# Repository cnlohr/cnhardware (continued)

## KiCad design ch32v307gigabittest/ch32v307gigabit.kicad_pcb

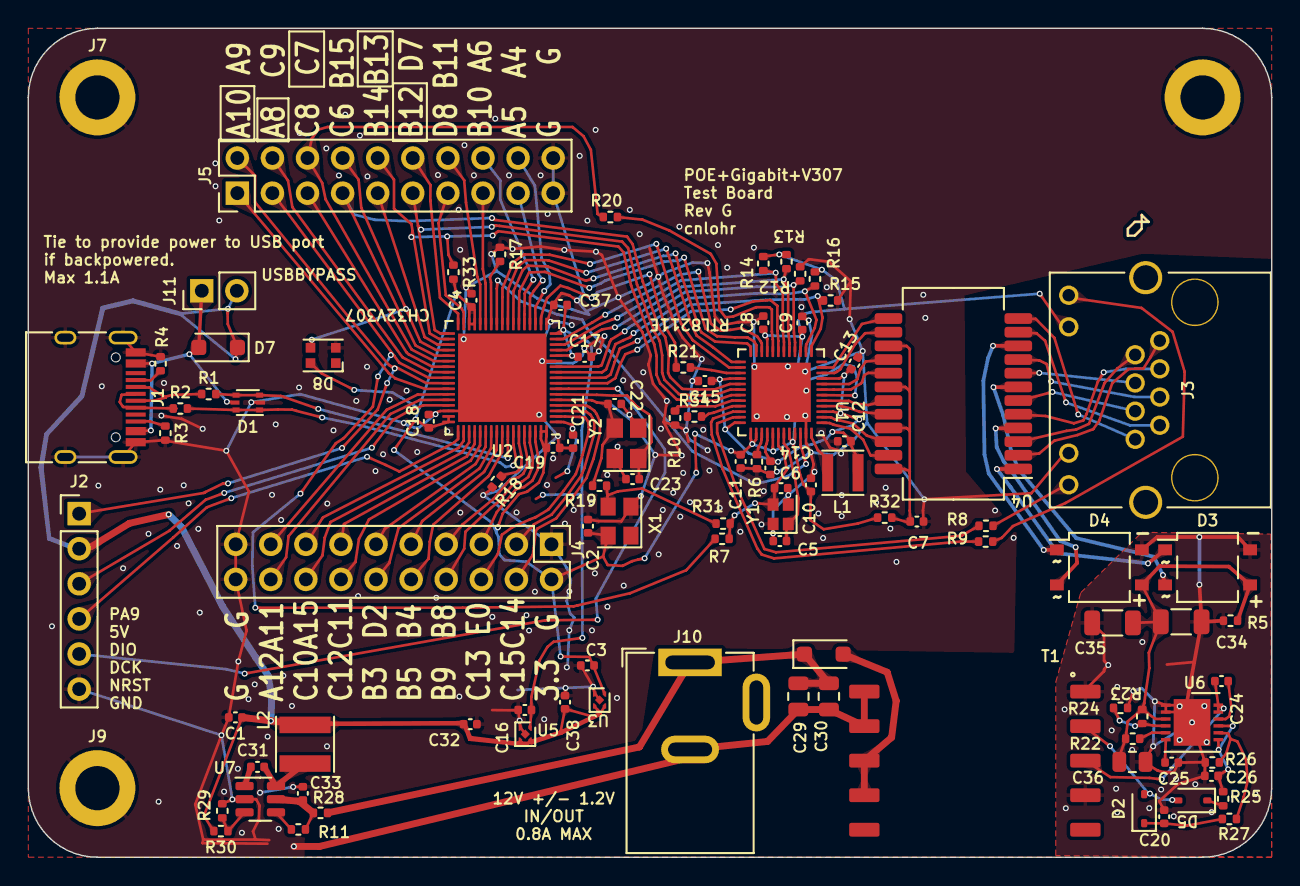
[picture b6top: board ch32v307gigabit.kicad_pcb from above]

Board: 2 copper layers, 90.0 x 60.0 mm, 101 parts (0 on the bottom side), 120 nets.

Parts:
C1, C3, C8, C12, C16, C21, C32: 4.7u; C_0402_1005Metric
C2, C26: 1u; C_0402_1005Metric
C4, C9, C10, C11, C13, C14, C15, C17, C18, C19, C25, C33, C37, C38: 0.1u; C_0402_1005Metric
C5, C6, C22, C23: 10p; C_0402_1005Metric
C7, C20, C24: 10n; C_0402_1005Metric
C29, C30: 25v10u; C_0805_2012Metric
C31: 22n; C_0402_1005Metric
C34, C35: 2.2u100v; C_1206_3216Metric
C36: 100v100n; C_0805_2012Metric
D1: USBLC6-2P6-TVS; SOT-666
D2, D5: D_SOD-323
D3, D4: RMBF; TO-269AA
D6, D7: D_SOD-123F
D8: WS2812B-2020; LED_WS2812B-2020_PLCC4_2.0x2.0mm
J1: USB_C_Receptacle_USB2.0; USB_C_Receptacle_HRO_TYPE-C-31-M-12
J2: PGM; PinHeader_1x06_P2.54mm_Vertical
J3: R-RJ45R08P-C000
J4, J5: AUX; PinHeader_2x10_P2.54mm_Vertical
J7, J8, J9: MH; MountingHole_3.2mm_M3_ISO14580_Pad
J10: Barrel; BarrelJack_GCT_DCJ200-10-A_Horizontal
J11: USBBYPASS; PinHeader_1x02_P2.54mm_Vertical
L1: 2.2uH 1.6A; L_Taiyo-Yuden_MD-3030
L2: 6.8uH 2A; L_Taiyo-Yuden_MD-4040
R1, R2, R25: 22; R_0402_1005Metric
R3, R4, R11: 5.1k; R_0402_1005Metric
R5, R24: 25k; R_0402_1005Metric
R6, R26, R29: 2.49k 1%; R_0402_1005Metric
R7, R19, R20, R21, R28: 0; R_0402_1005Metric
R8, R9: 1k; R_0402_1005Metric
R10, R12, R13, R14, R15, R16, R17, R18, R33: 4.7k; R_0402_1005Metric
R22, R23: 390k; R_0402_1005Metric
R27: 10k; R_0402_1005Metric
R30: 18k 1%; R_0402_1005Metric
R31, R32, R34: NP; R_0402_1005Metric
T1: TNK-TSA021-POE-TRANSFORMER
U1: RTL8211E-VB-CG; QFN-48-1EP_6x6mm_P0.4mm_EP4.3x4.3mm
U2: QFN-68-0.2mmpads-1EP_8x8mm_P0.4mm_EP6.4x6.4mm
U3, U5: 3.3vReg; xdfn-reg
U4: Transformer_Ethernet_YDS_30F-51NL_SO-24_7.1x15.1mm
U6: LM5160ADNTR; DFN-12-1EP_4x4mm_P0.5mm_EP2.66x3.38mm
U7: MT2492; SOT-23-6
X1: 8MHz TCXO; Oscillator_SMD_Abracon_ASE-4Pin_3.2x2.5mm
Y1: 25MHz; Crystal_SMD_2016-4Pin_2.0x1.6mm
Y2: 8MHz12pF; Crystal_SMD_3225-4Pin_3.2x2.5mm

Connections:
+3.3VA: C16.1, C17.1, C37.1, U2.13 (VDDA), U2.17 (VIO_4), U5.1 (OUT)
+3V3: C2.1, C3.1, C4.1, C8.1, C9.1, C10.1, C11.1, C18.1, C19.1, D8.4 (VDD), J3.10, J4.2, R13.2, R14.2, R16.2, R32.1, R33.2, U1.6 (AVDD33), U1.15 (DVDD33), U1.21 (DVDD33), U1.37 (DVDD33), U1.38 (ENSWREG), U1.41 (AVDD33), U1.44 (VDDREG), U1.45 (VDDREG), U2.31 (VIO_1), U2.32 (VDD_1), U2.50 (VDD_2), U2.51 (VIO_2), U2.67 (VIO_3), U2.68 (VDD_3), U3.1 (OUT), X1.4 (Vdd)
+5V: C1.1, C32.1, C38.1, D7.1 (K), J2.2, J11.2, L2.2, R30.2, U3.3 (EN), U3.4 (IN), U5.3 (EN), U5.4 (IN)
+12V: C29.1, C30.1, D6.1 (K), J10.1, R28.2
CT1: D4.1, U4.10 (MCT4)
CT2: D3.1, U4.1 (MCT1)
CT3: D4.2, U4.4 (MCT2)
CT4: D3.2, U4.7 (MCT3)
D+: D1.1 (IO1), D1.6 (IO1), R2.2, U2.62 (PB7/USB2DP)
D-: D1.3 (IO2), D1.4 (IO2), R1.2, U2.61 (PB6/USB2DM)
EPA4: J5.18, U2.20 (PA4/ADC4/DAC0)
EPA5: J5.17, U2.21 (PA5/ADC5/DAC1)
EPA6: J5.16, U2.22 (PA6/ADC6)
EPA9: J2.1, J5.2, U2.44 (PA9)
EPA10: J5.1, U2.45 (PA10)
EPA11: J4.17, U2.46 (PA11/USB1DM)
EPA12: J4.18, U2.47 (PA12/USB1DP)
EPA15: J4.15, U2.53 (PA15)
EPB3: J4.12, U2.58 (PB3)
EPB4: J4.9, U2.59 (PB4)
EPB5: J4.10, U2.60 (PB5)
EPB8: J4.7, U2.64 (PB8)
EPB9: J4.8, U2.65 (PB9)
EPB10: J5.15, U2.29 (PB10)
EPB11: J5.14, U2.30 (PB11)
EPB14: J5.9, U2.37 (PB14)
EPB15: D8.3 (DIN), J5.8, U2.38 (PB15)
EPC7: J5.6, R20.2, U2.40 (PC7/RXN)
EPC8: J5.5, U2.41 (PC8/TXP)
EPC9: J5.4, U2.42 (PC9/TXN)
EPC10: J4.16, U2.54 (PC10)
EPC11: J4.13, U2.55 (PC11)
EPC12: J4.14, U2.56 (PC12)
EPC13: J4.6, U2.2 (PC13)
EPC14: J4.3, U2.3 (PC14)
EPC15: J4.4, U2.4 (PC15)
EPD2: J4.11, U2.57 (PD2)
EPD8: J5.13, U2.33 (PD8)
EPD9: J5.12, U2.34 (PD9)
EPE0: J4.5, U2.66 (PE0)
GMII_CLK125: U1.46 (CLK125), U2.27 (PB1/ADC9)
GMII_MDC: J5.11, U1.30 (MDC), U2.35 (PB12)
GMII_MDIO: J5.10, R33.1, U1.31 (MDIO), U2.36 (PB13)
GMII_RXC: U1.19 (RXC), U2.8 (PC0/ADC10)
GMII_RXCTL: R15.1, U1.13 (RXCTL/PHY_AD), U2.9 (PC1/ADC11)
GMII_RXD0: R16.1, U1.14 (RXD0/SELRGV), U2.10 (PC2/ADC12)
GMII_RXD1: R12.1, U1.16 (RXD1/TXDLY), U2.11 (PC3/ADC13)
GMII_RXD2: R13.1, U1.17 (RXD2/AN0), U2.14 (PA0/ADC0)
GMII_RXD3: R14.1, U1.18 (RXD3/AN1), U2.15 (PA1/ADC1)
GMII_TXC: U1.22 (TXC), U2.16 (PA2/ADC2)
GMII_TXCTL: R21.1, U2.19 (PA3/ADC3)
GMII_TXD0: U1.23 (TXD0), U2.23 (PA7/ADC7)
GMII_TXD1: U1.24 (TXD1), U2.24 (PC4/ADC14)
GMII_TXD2: U1.25 (TXD2), U2.25 (PC5/ADC15)
GMII_TXD3: U1.26 (TXD3), U2.26 (PB0/ADC8)
GND: C1.2, C2.2, C3.2, C4.2, C5.1, C6.1, C7.2, C8.2, C9.2, C10.2, C11.2, C12.2, C13.2, C14.2, C15.2, C16.2, C17.2, C18.2, C19.2, C21.2, C22.1, C23.1, C29.2, C30.2, C32.2, C33.2, C37.2, C38.2, D1.2 (GND), D8.2 (VSS), J1.A1 (GND), J1.A12 (GND), J1.B1 (GND), J1.B12 (GND), J1.S1 (SHIELD), J2.6, J3.11, J4.1, J4.19, J4.20, J5.19, J5.20, J7.1, J8.1, J9.1, J10.2, R3.2, R4.2, R6.2, R10.2, R12.2, R15.2, R17.1, R18.2, R29.1, R34.1, T1.9 (SECA-), T1.10 (SECB-), U1.47 (GND), U1.49 (GND), U2.12 (VSSA), U2.18 (VSS_1), U2.49 (VSS_2), U2.69 (GND), U3.2 (GND), U3.5 (GND), U5.2 (GND), U5.5 (GND), U7.2 (GND), X1.2 (GND), Y1.2, Y1.4, Y2.2, Y2.4
LED0: J3.9, R9.1
LED1: J3.12, R8.1
NRST: J2.5, U2.7 (NRST)
unnamed: D2.2 (A), D5.2 (A), T1.2 (BIAS+)
unnamed: C20.2, D2.1 (K), R27.2
unnamed: D5.1 (K), R25.2
unnamed: J1.A5 (CC1), R4.1
unnamed: J1.B5 (CC2), R3.1
unnamed: J1.A6 (D+), J1.B6 (D+), R2.1
unnamed: J1.A7 (D-), J1.B7 (D-), R1.1
unnamed: C24.2, T1.3 (PRI+), U6.11 (SW), U6.12 (SW)
unnamed: C6.2, R7.2, R31.2, U1.42 (CKXTAL1), Y1.3
unnamed: C5.2, U1.43 (CKXTAL2), Y1.1
unnamed: R20.1, U1.20 (INTB)
unnamed: R9.2, U1.34 (LED0/PHY_AD0)
unnamed: R8.2, U1.35 (LED1/PHY_AD1)
unnamed: U1.1 (MDI[0]+), U4.23 (TX1+)
unnamed: U1.2 (MDI[0]-), U4.22 (TX1-)
unnamed: U1.4 (MDI[1]+), U4.20 (TX2+)
unnamed: U1.5 (MDI[1]-), U4.19 (TX2-)
unnamed: U1.7 (MDI[2]+), U4.17 (TX3+)
unnamed: U1.8 (MDI[2]-), U4.16 (TX3-)
unnamed: U1.10 (MDI[3]+), U4.14 (TX4+)
unnamed: U1.11 (MDI[3]-), U4.13 (TX4-)
unnamed: R34.2, U1.33 (PEMB)
unnamed: L1.1, U1.48 (REG_OUT)
unnamed: R6.1, U1.39 (RSET)
unnamed: R21.2, U1.27 (TXCTL)
unnamed: R18.1, U2.63 (BOOT0)
unnamed: R17.2, U2.28 (PB2/BOOT1)
unnamed: C21.1, U2.1 (VBAT)
unnamed: J3.1, U4.2 (MD1+)
unnamed: J3.2, U4.3 (MD1-)
unnamed: J3.3, U4.5 (MD2+)
unnamed: J3.6, U4.6 (MD2-)
unnamed: J3.4, U4.8 (MD3+)
unnamed: J3.5, U4.9 (MD3-)
unnamed: J3.7, U4.11 (MD4+)
unnamed: J3.8, U4.12 (MD4-)
unnamed: C7.1, R32.2, U4.15 (TCT4), U4.18 (TCT3), U4.21 (TCT2), U4.24 (TCT1)
unnamed: C24.1, U6.10 (BST)
unnamed: R23.2, R24.1, U6.4 (EN/UVLO)
unnamed: R26.2, R27.1, U6.8 (FB)
unnamed: C26.1, R25.1, U6.7 (FPWM), U6.9 (VCC)
unnamed: R22.2, U6.5 (RON)
unnamed: C25.1, U6.6 (SS)
unnamed: C31.1, U7.1 (BS)
unnamed: R11.1, U7.4 (EN)
unnamed: R29.2, R30.1, U7.3 (FB)
unnamed: C31.2, L2.1, U7.6 (SW)
unnamed: C33.1, R11.2, R28.1, U7.5 (VIN)
OSCI: C22.2, R19.2, U2.5 (PD0/OSCIN), Y2.3
OSCO: C23.2, U2.6 (PD1/OSCOUT), Y2.1
PHY_10: C12.1, C13.1, C14.1, C15.1, L1.2, U1.3 (AVDD10), U1.9 (AVDD10), U1.28 (DVDD10), U1.36 (DVDD10), U1.40 (AVDD10)
PHY_CKTAL: J5.3, R7.1, U2.43 (PA8)
PHY_RSTB: J5.7, U1.29 (PHYRSTB), U2.39 (PC6/RXP)
POE+: C34.1, C35.1, C36.1, D3.3 (+), D4.3 (+), R5.1, R22.1, R23.1, U6.3 (VIN)
POE-: C20.1, C25.2, C26.2, C34.2, C35.2, C36.2, D3.4 (-), D4.4 (-), R5.2, R24.2, R26.1, T1.1 (BIAS-), T1.4 (PRI-), U6.1 (AGND), U6.2 (PGND), U6.13 (AGND)
POE-MO: D6.2 (A), T1.7 (SECA+), T1.8 (SECB+)
RXDLY: R10.1, U1.32 (LED2/RXDLY)
SWCLK: J2.4, U2.52 (PA14/SWCLK)
SWIO: J2.3, U2.48 (PA13/SWIO)
TCXOO: R19.1, R31.1, X1.3 (OUT)
VB: D1.5 (VB), D7.2 (A), J1.A4 (VBUS), J1.A9 (VBUS), J1.B4 (VBUS), J1.B9 (VBUS), J11.1

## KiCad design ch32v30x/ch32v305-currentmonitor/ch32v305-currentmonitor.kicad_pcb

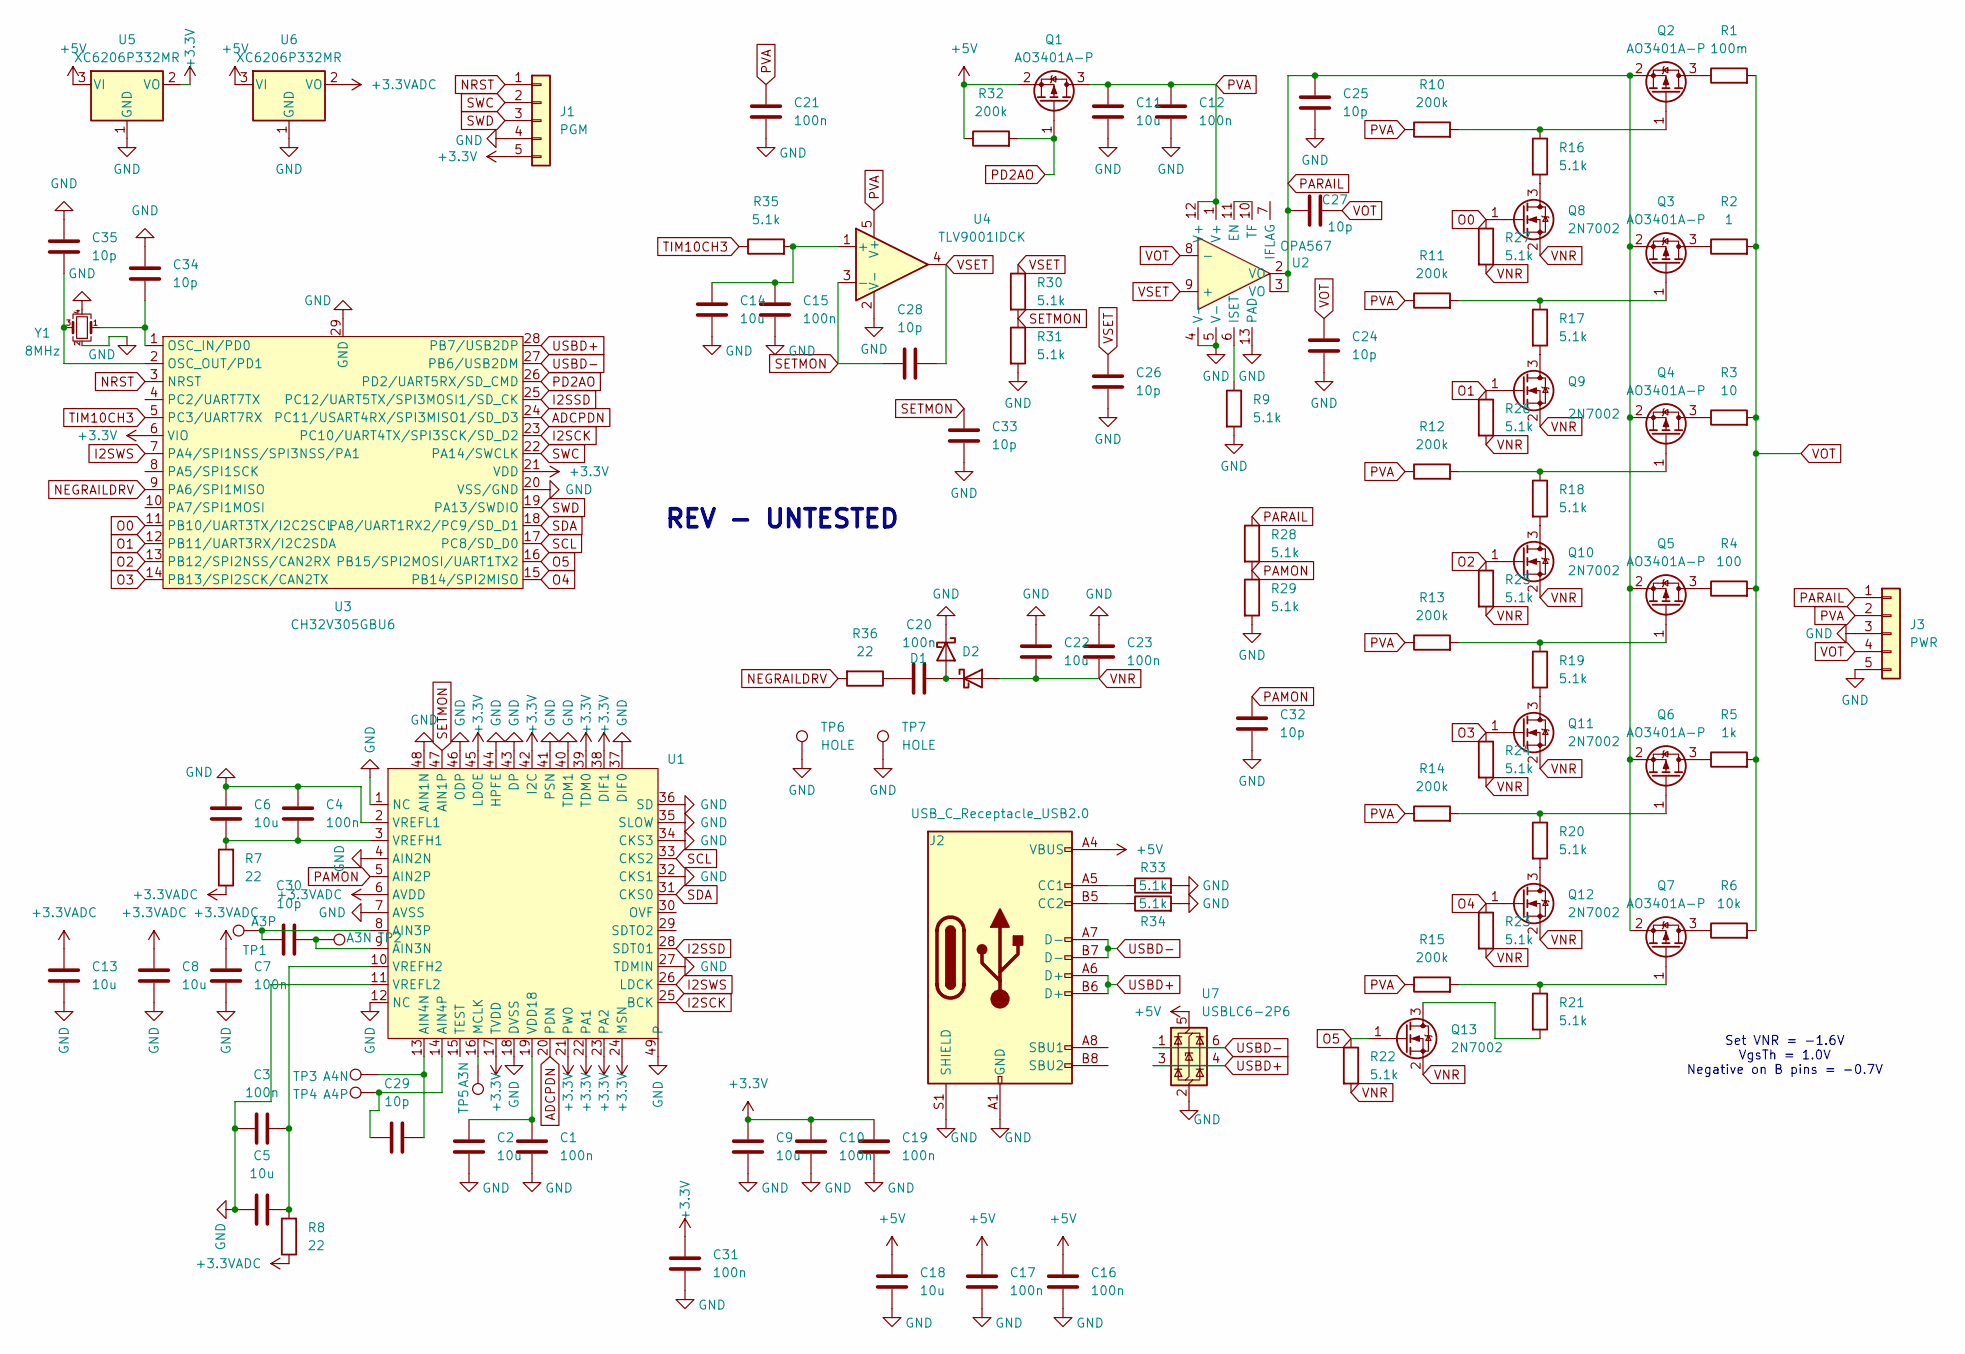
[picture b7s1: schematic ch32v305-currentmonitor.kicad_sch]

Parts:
C1, C3, C4, C7, C10, C12, C15, C16, C17, C19, C20, C21, C23, C31: 100n; C_0402_1005Metric; LCSC C1525
C2, C5, C6, C8, C9, C11, C13, C14, C18, C22: 10u; C_0603_1608Metric; LCSC C19702
C24, C25, C26, C27, C28, C29, C30, C32, C33, C34, C35: 10p; C_0402_1005Metric; LCSC C32949
D1, D2: D_Schottky; D_SOD-323; LCSC C191023
J1: PGM; PinHeader_1x05_P2.54mm_Vertical; LCSC C492404
J2: USB_C_Receptacle_USB2.0; USB_C_Receptacle_HRO_TYPE-C-31-M-12; LCSC C2765186
J3: PWR; PinHeader_1x05_P2.54mm_Vertical; LCSC C492404
Q1, Q2, Q3, Q4, Q5, Q6, Q7: AO3401A-P; SOT-23; LCSC C15127
Q8, Q9, Q10, Q11, Q12, Q13: 2N7002; SOT-23; LCSC C8545
R1: 100m; R_1206_3216Metric; LCSC C25334
R2: 1; R_1206_3216Metric; LCSC C17928
R3: 10; R_1206_3216Metric; LCSC C17903
R4: 100; R_1206_3216Metric; LCSC C17901
R5: 1k; R_1206_3216Metric; LCSC C4410
R6: 10k; R_1206_3216Metric; LCSC C17902
R7, R8, R36: 22; R_0402_1005Metric_COMPACT; LCSC C25092
R9, R16, R17, R18, R19, R20, R21, R22, R23, R24, R25, R26, R27, R28, R29, R30, R31, R35: 5.1k; R_0402_1005Metric_COMPACT; LCSC C25905
R10, R11, R12, R13, R14, R15, R32: 200k; R_0402_1005Metric_COMPACT; LCSC C25764
R33, R34: 5.1k; R_0402_1005Metric; LCSC C105872
TP1: A3P; TestPoint_Pad_D1.5mm
TP2, TP5: A3N; TestPoint_Pad_D1.5mm
TP3: A4N; TestPoint_Pad_D1.5mm
TP4: A4P; TestPoint_Pad_D1.5mm
TP6, TP7: HOLE; MountingHole_3.2mm_M3_Pad_Via
U1: QFN-48-1EP_7x7mm_P0.5mm_EP5.1x5.1mm; LCSC C2667243
U2: OPA567; OPA567-QFN-12; LCSC C2058524
U3: CH32V305GBU6; QFN-28-1EP_4x4mm_P0.4mm_EP2.3x2.3mm; LCSC C19100608
U4: TLV9001IDCK; SOT-353_SC-70-5; LCSC C398363
U5, U6: XC6206P332MR; SOT-23-3; LCSC C5446
U7: USBLC6-2P6; SOT-666; LCSC C2827693
Y1: 8MHz; Crystal_SMD_3225-4Pin_3.2x2.5mm; LCSC C2973805

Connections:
+3.3V: C9.1, C10.1, C19.1, C31.1, J1.5, U1.17 (TVDD), U1.21 (PW0), U1.22 (PA1), U1.23 (PA2), U1.24 (MSN), U1.38 (DIF1), U1.39 (TDM0), U1.42 (I2C), U1.45 (LDOE), U3.6 (VIO), U3.21 (VDD), U5.2 (VO)
+3.3VADC: C7.2, C8.2, C13.2, R7.1, R8.1, U1.6 (AVDD), U6.2 (VO)
+5V: C16.1, C17.1, C18.1, J2.A4 (VBUS), J2.A9 (VBUS), J2.B4 (VBUS), J2.B9 (VBUS), Q1.2 (S), R32.1, U5.3 (VI), U6.3 (VI), U7.5 (VBUS)
ADCPDN: U1.20 (PDN), U3.24 (PC11/USART4RX/SPI3MISO1/SD_D3)
GND: C1.2, C2.2, C3.1, C4.2, C5.1, C6.2, C7.1, C8.1, C9.2, C10.2, C11.2, C12.2, C13.1, C14.2, C15.2, C16.2, C17.2, C18.2, C19.2, C21.2, C22.1, C23.1, C24.2, C25.2, C26.2, C31.2, C32.1, C33.2, C34.2, C35.2, D1.1 (K), J1.4, J2.A1 (GND), J2.A12 (GND), J2.B1 (GND), J2.B12 (GND), J2.S1 (SHIELD), J3.3, J3.5, R9.2, R29.2, R31.2, R33.2, R34.2, TP6.1, TP7.1, U1.1 (NC), U1.2 (VREFL1), U1.4 (AIN2N), U1.7 (AVSS), U1.11 (VREFL2), U1.12 (NC), U1.18 (DVSS), U1.27 (TDMIN), U1.32 (CKS1), U1.34 (CKS3), U1.35 (SLOW), U1.36 (SD), U1.37 (DIF0), U1.40 (TDM1), U1.41 (PSN), U1.43 (DP), U1.44 (HPFE), U1.46 (ODP), U1.48 (AIN1N), U1.49, U2.4 (V-), U2.5 (V-), U2.13 (PAD), U3.20 (VSS/GND), U3.29 (GND), U4.2 (V-), U5.1 (GND), U6.1 (GND), U7.2 (GND), Y1.2, Y1.4
I2SCK: U1.25 (BCK), U3.23 (PC10/UART4TX/SPI3SCK/SD_D2)
I2SSD: U1.28 (SDT01), U3.25 (PC12/UART5TX/SPI3MOSI1/SD_CK)
I2SWS: U1.26 (LDCK), U3.7 (PA4/SPI1NSS/SPI3NSS/PA1)
NEGRAILDRV: R36.2, U3.9 (PA6/SPI1MISO)
NRST: J1.1, U3.3 (NRST)
unnamed: C20.1, R36.1
unnamed: C20.2, D1.2 (A), D2.1 (K)
unnamed: J2.A5 (CC1), R33.1
unnamed: J2.B5 (CC2), R34.1
unnamed: Q2.3 (D), R1.1
unnamed: Q2.1 (G), R10.2, R16.1
unnamed: Q3.3 (D), R2.1
unnamed: Q3.1 (G), R11.2, R17.1
unnamed: Q4.3 (D), R3.1
unnamed: Q4.1 (G), R12.2, R18.1
unnamed: Q5.3 (D), R4.1
unnamed: Q5.1 (G), R13.2, R19.1
unnamed: Q6.3 (D), R5.1
unnamed: Q6.1 (G), R14.2, R20.1
unnamed: Q7.3 (D), R6.1
unnamed: Q7.1 (G), R15.2, R21.1
unnamed: Q8.3 (D), R16.2
unnamed: Q9.3 (D), R17.2
unnamed: Q10.3 (D), R18.2
unnamed: Q11.3 (D), R19.2
unnamed: Q12.3 (D), R20.2
unnamed: Q13.3 (D), R21.2
unnamed: C30.2, TP2.1, U1.9 (AIN3N)
unnamed: C30.1, TP1.1, U1.8 (AIN3P)
unnamed: C29.2, TP3.1, U1.13 (AIN4N)
unnamed: C29.1, TP4.1, U1.14 (AIN4P)
unnamed: TP5.1, U1.16 (MCLK)
unnamed: C1.1, C2.1, U1.19 (VDD18)
unnamed: C4.1, C6.1, R7.2, U1.3 (VREFH1)
unnamed: C3.2, C5.2, R8.2, U1.10 (VREFH2)
unnamed: U2.10 (TF), U2.11 (EN)
unnamed: R9.1, U2.6 (ISET)
unnamed: C34.1, U3.1 (OSC_IN/PD0), Y1.1
unnamed: C35.1, U3.2 (OSC_OUT/PD1), Y1.3
unnamed: C14.1, C15.1, R35.2, U4.1 (+)
O0: Q8.1 (G), R27.1, U3.11 (PB10/UART3TX/I2C2SCL)
O1: Q9.1 (G), R26.1, U3.12 (PB11/UART3RX/I2C2SDA)
O2: Q10.1 (G), R25.1, U3.13 (PB12/SPI2NSS/CAN2RX)
O3: Q11.1 (G), R24.1, U3.14 (PB13/SPI2SCK/CAN2TX)
O4: Q12.1 (G), R23.1, U3.15 (PB14/SPI2MISO)
O5: Q13.1 (G), R22.1, U3.16 (PB15/SPI2MOSI/UART1TX2)
PAMON: C32.2, R28.2, R29.1, U1.5 (AIN2P)
PARAIL: C25.1, C27.1, J3.1, Q2.2 (S), Q3.2 (S), Q4.2 (S), Q5.2 (S), Q6.2 (S), Q7.2 (S), R28.1, U2.2 (VO), U2.3 (VO)
PD2AO: Q1.1 (G), R32.2, U3.26 (PD2/UART5RX/SD_CMD)
PVA: C11.1, C12.1, C21.1, J3.2, Q1.3 (D), R10.1, R11.1, R12.1, R13.1, R14.1, R15.1, U2.1 (V+), U2.12 (V+), U4.5 (V+)
SCL: U1.33 (CKS2), U3.17 (PC8/SD_D0)
SDA: U1.31 (CKS0), U3.18 (PA8/UART1RX2/PC9/SD_D1)
SETMON: C28.1, C33.1, R30.2, R31.1, U1.47 (AIN1P), U4.3 (-)
SWC: J1.2, U3.22 (PA14/SWCLK)
SWD: J1.3, U3.19 (PA13/SWDIO)
TIM10CH3: R35.1, U3.5 (PC3/UART7RX)
USBD+: J2.A6 (D+), J2.B6 (D+), U3.28 (PB7/USB2DP), U7.3 (I/O2), U7.4 (I/O2)
USBD-: J2.A7 (D-), J2.B7 (D-), U3.27 (PB6/USB2DM), U7.1 (I/O1), U7.6 (I/O1)
VNR: C22.2, C23.2, D2.2 (A), Q8.2 (S), Q9.2 (S), Q10.2 (S), Q11.2 (S), Q12.2 (S), Q13.2 (S), R22.2, R23.2, R24.2, R25.2, R26.2, R27.2
VOT: C24.1, C27.2, J3.4, R1.2, R2.2, R3.2, R4.2, R5.2, R6.2, U2.8 (-)
VSET: C26.1, C28.2, R30.1, U2.9 (+), U4.4

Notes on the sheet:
REV - UNTESTED
Set VNR = -1.6V VgsTh = 1.0V Negative on B pins = -0.7V

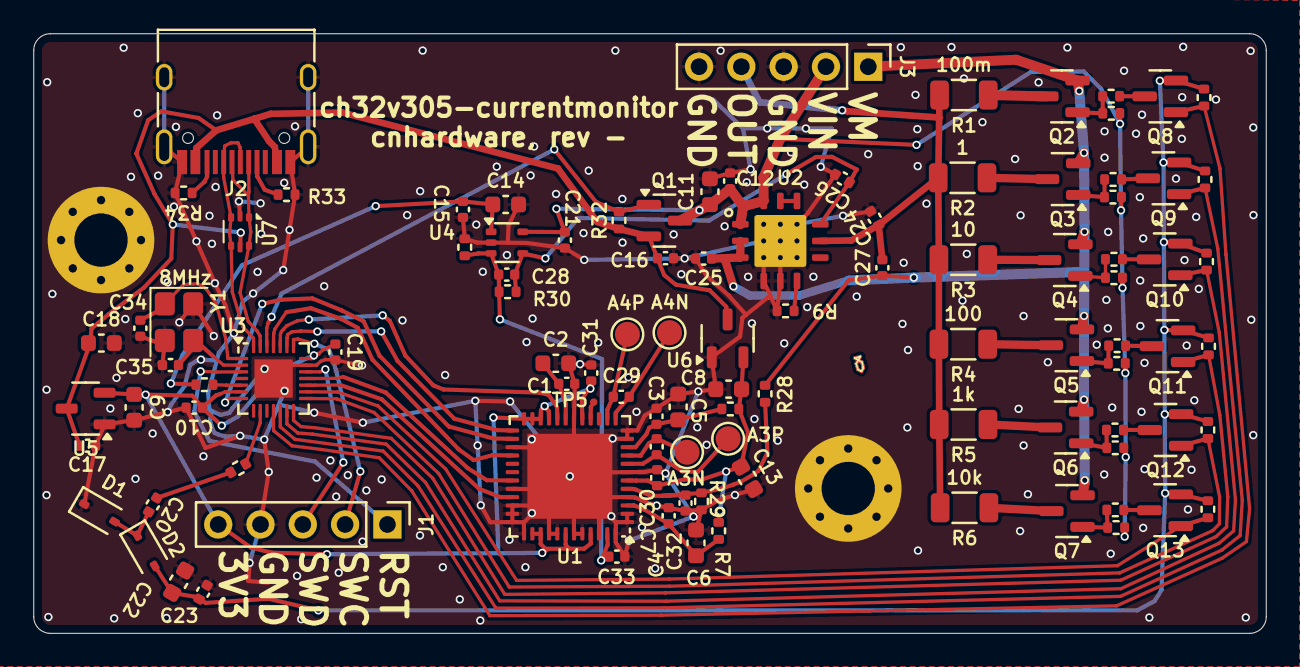
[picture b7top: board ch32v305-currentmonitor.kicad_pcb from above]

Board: 2 copper layers, 74.0 x 36.0 mm, 104 parts (0 on the bottom side), 66 nets.

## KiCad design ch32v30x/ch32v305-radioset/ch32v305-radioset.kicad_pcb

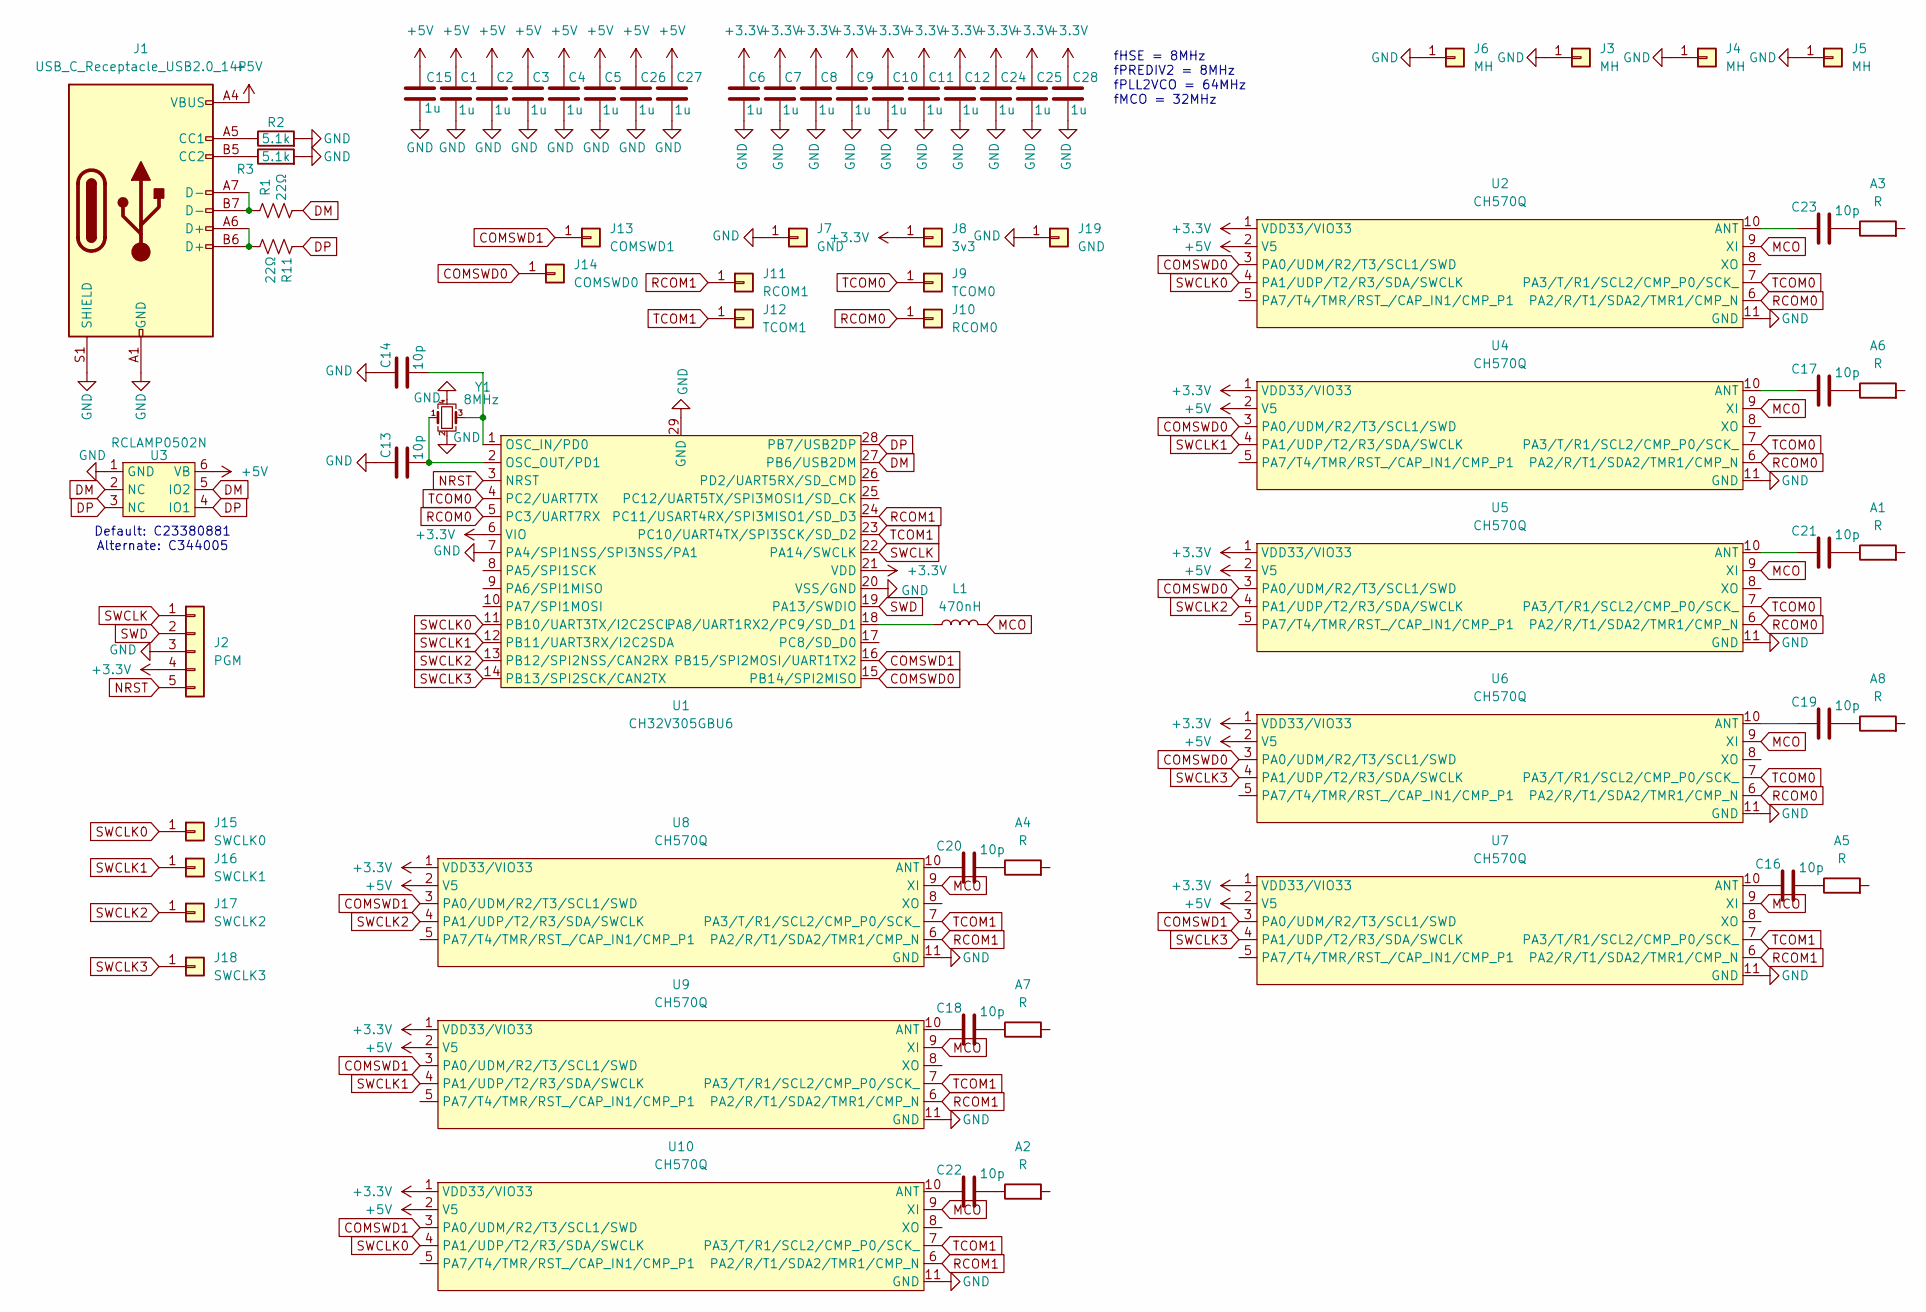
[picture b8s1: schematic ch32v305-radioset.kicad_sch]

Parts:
A1, A2, A3, A4: R; Coilcraft_MA5532-AE_RFID; LCSC C99665
A5, A6, A7, A8: R; R_2010_5025Metric; LCSC C22467691
C1, C2, C3, C4, C5, C6, C7, C8, C9, C10, C11, C12, C15, C24, C25, C26, C27, C28: 1u; C_0402_1005Metric; LCSC C52923
C13, C14, C16, C17, C18, C19, C20, C21, C22, C23: 10p; C_0402_1005Metric; LCSC C32949
J1: USB_C_Receptacle_USB2.0_14P; USB_C_MOD_Receptacle_HRO_TYPE-C-31-M-12; LCSC C2765186
J2: PGM; PinHeader_1x05_P2.54mm_Vertical; LCSC C124379
J3, J4, J5, J6: MH; MountingHole_3.2mm_M3_DIN965_Pad
J7, J19: GND; TestPoint_Pad_D1.5mm
J8: 3v3; TestPoint_Pad_D1.5mm
J9: TCOM0; TestPoint_Pad_D1.5mm
J10: RCOM0; TestPoint_Pad_D1.5mm
J11: RCOM1; TestPoint_Pad_D1.5mm
J12: TCOM1; TestPoint_Pad_D1.5mm
J13: COMSWD1; TestPoint_Pad_D1.5mm
J14: COMSWD0; TestPoint_Pad_D1.5mm
J15: SWCLK0; TestPoint_Pad_D1.5mm
J16: SWCLK1; TestPoint_Pad_D1.5mm
J17: SWCLK2; TestPoint_Pad_D1.5mm
J18: SWCLK3; TestPoint_Pad_D1.5mm
L1: 470nH; L_0603_1608Metric; LCSC C84476
R1, R11: 22Ω; R_0402_1005Metric_COMPACT; LCSC C25092
R2, R3: 5.1k; R_0402_1005Metric; LCSC C25905
U1: CH32V305GBU6; QFN-28-1EP_4x4mm_P0.4mm_EP2.3x2.3mm; LCSC C19100608
U2, U4, U5, U6, U7, U8, U9, U10: CH570Q; DFN-10-1EP_3x3mm_P0.5mm_EP1.7x2.5mm; LCSC C49260680
U3: RCLAMP0502N; DFN-6_1.2x1.0mm_P0.4mm; LCSC C344005
Y1: 8MHz; Crystal_SMD_3225-4Pin_3.2x2.5mm; LCSC C2973805

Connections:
+3.3V: C6.1, C7.1, C8.1, C9.1, C10.1, C11.1, C12.1, C24.1, C25.1, C28.1, J2.4, J8.1, U1.6 (VIO), U1.21 (VDD), U2.1 (VDD33/VIO33), U4.1 (VDD33/VIO33), U5.1 (VDD33/VIO33), U6.1 (VDD33/VIO33), U7.1 (VDD33/VIO33), U8.1 (VDD33/VIO33), U9.1 (VDD33/VIO33), U10.1 (VDD33/VIO33)
+5V: C1.1, C2.1, C3.1, C4.1, C5.1, C15.1, C26.1, C27.1, J1.A4 (VBUS), J1.A9 (VBUS), J1.B4 (VBUS), J1.B9 (VBUS), U2.2 (V5), U3.6 (VB), U4.2 (V5), U5.2 (V5), U6.2 (V5), U7.2 (V5), U8.2 (V5), U9.2 (V5), U10.2 (V5)
COMSWD0: J14.1, U1.15 (PB14/SPI2MISO), U2.3 (PA0/UDM/R2/T3/SCL1/SWD), U4.3 (PA0/UDM/R2/T3/SCL1/SWD), U5.3 (PA0/UDM/R2/T3/SCL1/SWD), U6.3 (PA0/UDM/R2/T3/SCL1/SWD)
COMSWD1: J13.1, U1.16 (PB15/SPI2MOSI/UART1TX2), U7.3 (PA0/UDM/R2/T3/SCL1/SWD), U8.3 (PA0/UDM/R2/T3/SCL1/SWD), U9.3 (PA0/UDM/R2/T3/SCL1/SWD), U10.3 (PA0/UDM/R2/T3/SCL1/SWD)
DM: R1.2, U1.27 (PB6/USB2DM), U3.2 (NC), U3.5 (IO2)
DP: R11.1, U1.28 (PB7/USB2DP), U3.3 (NC), U3.4 (IO1)
GND: C1.2, C2.2, C3.2, C4.2, C5.2, C6.2, C7.2, C8.2, C9.2, C10.2, C11.2, C12.2, C13.1, C14.1, C15.2, C24.2, C25.2, C26.2, C27.2, C28.2, J1.A1 (GND), J1.A12 (GND), J1.B1 (GND), J1.B12 (GND), J1.S1 (SHIELD), J2.3, J3.1, J4.1, J5.1, J6.1, J7.1, J19.1, R2.2, R3.2, U1.7 (PA4/SPI1NSS/SPI3NSS/PA1), U1.20 (VSS/GND), U1.29 (GND), U2.11 (GND), U3.1 (GND), U4.11 (GND), U5.11 (GND), U6.11 (GND), U7.11 (GND), U8.11 (GND), U9.11 (GND), U10.11 (GND), Y1.2, Y1.4
MCO: L1.2, U2.9 (XI), U4.9 (XI), U5.9 (XI), U6.9 (XI), U7.9 (XI), U8.9 (XI), U9.9 (XI), U10.9 (XI)
NRST: J2.5, U1.3 (NRST)
unnamed: A1.1, C21.2
unnamed: A2.1, C22.2
unnamed: A3.1, C23.2
unnamed: A4.1, C20.2
unnamed: A5.1, C16.2
unnamed: A6.1, C17.2
unnamed: A7.1, C18.2
unnamed: A8.1, C19.2
unnamed: J1.A5 (CC1), R2.1
unnamed: J1.B5 (CC2), R3.1
unnamed: J1.A6 (D+), J1.B6 (D+), R11.2
unnamed: J1.A7 (D-), J1.B7 (D-), R1.1
unnamed: C14.2, U1.1 (OSC_IN/PD0), Y1.3
unnamed: C13.2, U1.2 (OSC_OUT/PD1), Y1.1
unnamed: L1.1, U1.18 (PA8/UART1RX2/PC9/SD_D1)
unnamed: C23.1, U2.10 (ANT)
unnamed: C17.1, U4.10 (ANT)
unnamed: C21.1, U5.10 (ANT)
unnamed: C19.1, U6.10 (ANT)
unnamed: C16.1, U7.10 (ANT)
unnamed: C20.1, U8.10 (ANT)
unnamed: C18.1, U9.10 (ANT)
unnamed: C22.1, U10.10 (ANT)
RCOM0: J10.1, U1.5 (PC3/UART7RX), U2.6 (PA2/R/T1/SDA2/TMR1/CMP_N), U4.6 (PA2/R/T1/SDA2/TMR1/CMP_N), U5.6 (PA2/R/T1/SDA2/TMR1/CMP_N), U6.6 (PA2/R/T1/SDA2/TMR1/CMP_N)
RCOM1: J11.1, U1.24 (PC11/USART4RX/SPI3MISO1/SD_D3), U7.6 (PA2/R/T1/SDA2/TMR1/CMP_N), U8.6 (PA2/R/T1/SDA2/TMR1/CMP_N), U9.6 (PA2/R/T1/SDA2/TMR1/CMP_N), U10.6 (PA2/R/T1/SDA2/TMR1/CMP_N)
SWCLK: J2.1, U1.22 (PA14/SWCLK)
SWCLK0: J15.1, U1.11 (PB10/UART3TX/I2C2SCL), U2.4 (PA1/UDP/T2/R3/SDA/SWCLK), U10.4 (PA1/UDP/T2/R3/SDA/SWCLK)
SWCLK1: J16.1, U1.12 (PB11/UART3RX/I2C2SDA), U4.4 (PA1/UDP/T2/R3/SDA/SWCLK), U9.4 (PA1/UDP/T2/R3/SDA/SWCLK)
SWCLK2: J17.1, U1.13 (PB12/SPI2NSS/CAN2RX), U5.4 (PA1/UDP/T2/R3/SDA/SWCLK), U8.4 (PA1/UDP/T2/R3/SDA/SWCLK)
SWCLK3: J18.1, U1.14 (PB13/SPI2SCK/CAN2TX), U6.4 (PA1/UDP/T2/R3/SDA/SWCLK), U7.4 (PA1/UDP/T2/R3/SDA/SWCLK)
SWD: J2.2, U1.19 (PA13/SWDIO)
TCOM0: J9.1, U1.4 (PC2/UART7TX), U2.7 (PA3/T/R1/SCL2/CMP_P0/SCK_), U4.7 (PA3/T/R1/SCL2/CMP_P0/SCK_), U5.7 (PA3/T/R1/SCL2/CMP_P0/SCK_), U6.7 (PA3/T/R1/SCL2/CMP_P0/SCK_)
TCOM1: J12.1, U1.23 (PC10/UART4TX/SPI3SCK/SD_D2), U7.7 (PA3/T/R1/SCL2/CMP_P0/SCK_), U8.7 (PA3/T/R1/SCL2/CMP_P0/SCK_), U9.7 (PA3/T/R1/SCL2/CMP_P0/SCK_), U10.7 (PA3/T/R1/SCL2/CMP_P0/SCK_)

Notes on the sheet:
Default: C23380881 Alternate: C344005
fHSE = 8MHz fPREDIV2 = 8MHz fPLL2VCO = 64MHz fMCO = 32MHz

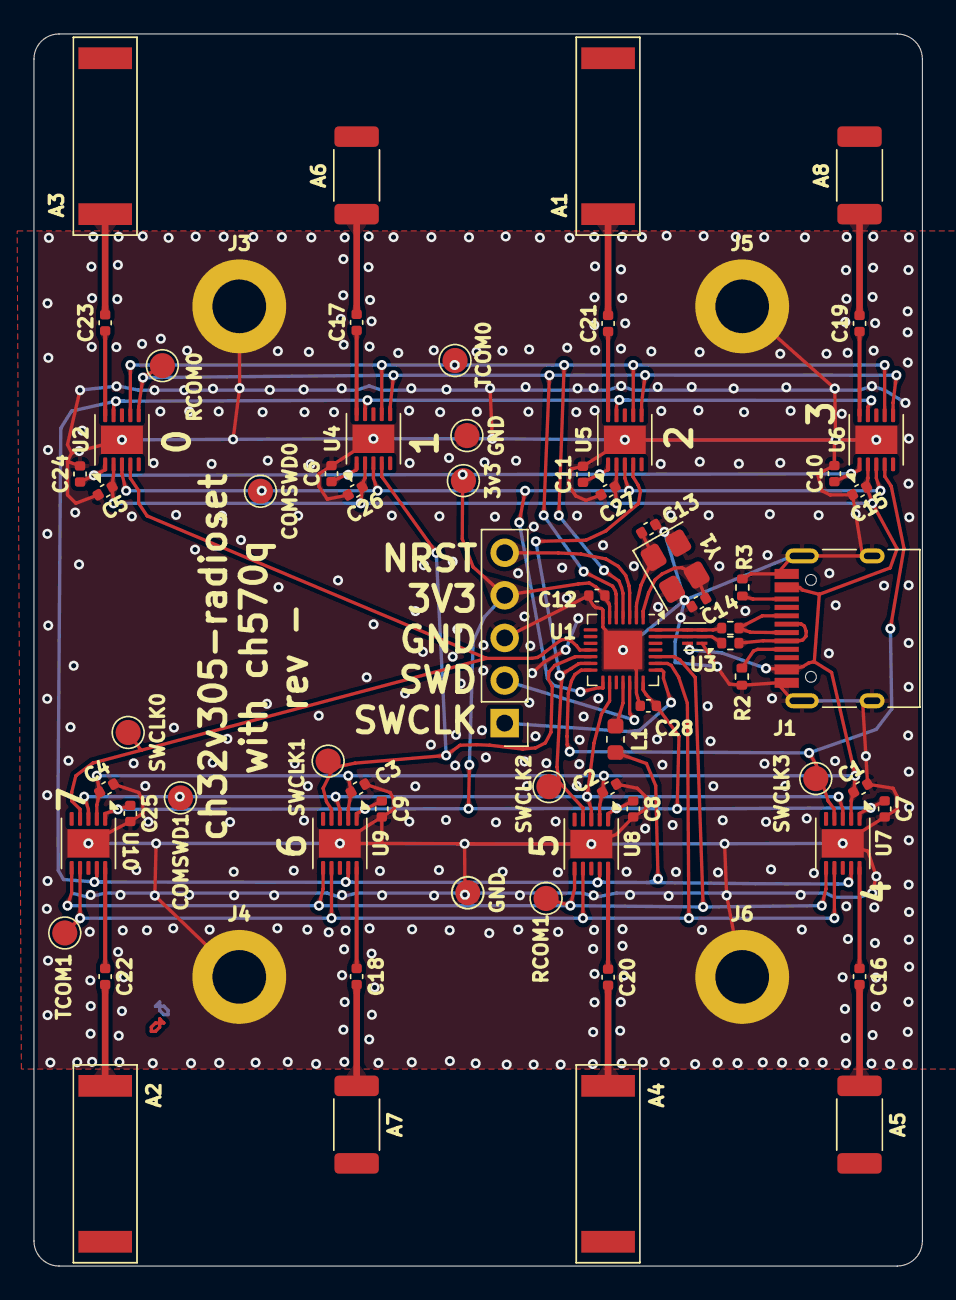
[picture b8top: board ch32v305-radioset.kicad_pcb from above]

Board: 2 copper layers, 53.0 x 73.5 mm, 71 parts (0 on the bottom side), 42 nets.
